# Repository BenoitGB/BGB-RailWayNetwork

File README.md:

# BenoitBG

Electronics and Software Projects for Scale Model Railroad

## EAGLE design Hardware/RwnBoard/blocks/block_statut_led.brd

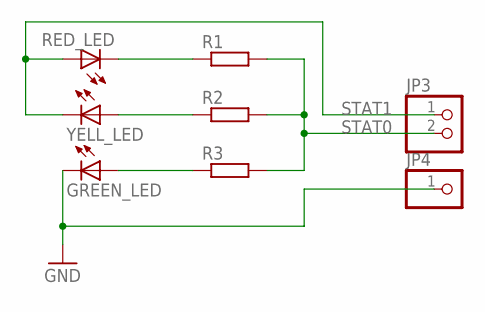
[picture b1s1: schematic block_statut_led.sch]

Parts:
GREEN_LED: LED3MM
JP3: PINHD-1X2; 1X02
JP4: PINHD-1X1; 1X01
R1, R2, R3: R-EU_0207/5V; 0207/5V
RED_LED: LED3MM
YELL_LED: LED3MM

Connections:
GND: GREEN_LED.K (C), JP4.1
unnamed: R1.1, RED_LED.K (C)
unnamed: R2.1, YELL_LED.A
unnamed: GREEN_LED.A, R3.1
STAT0: JP3.2, R1.2, R2.2, R3.2
STAT1: JP3.1, RED_LED.A, YELL_LED.K (C)

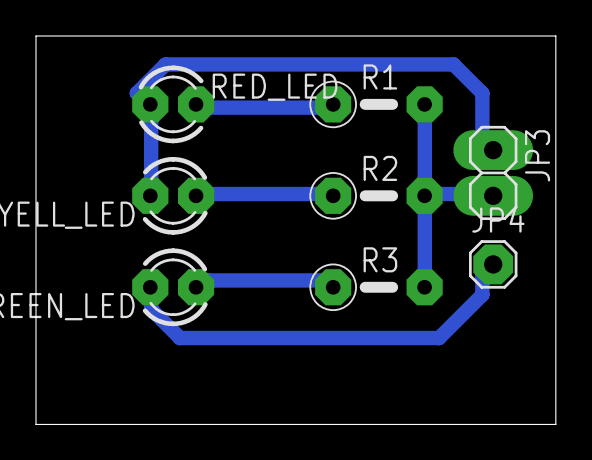
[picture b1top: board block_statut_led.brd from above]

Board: 2 copper layers, 28.9 x 21.6 mm, 8 parts (0 on the bottom side), 6 nets.

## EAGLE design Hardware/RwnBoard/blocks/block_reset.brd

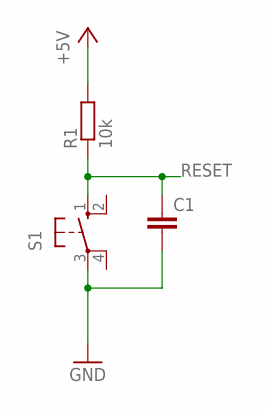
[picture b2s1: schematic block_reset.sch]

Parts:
C1: C-EU050-024X044; C050-024X044
R1: 10k; 0207/10
S1: 10-XX; B3F-10XX

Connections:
+5V: R1.2
GND: C1.2, S1.3
RESET: C1.1, R1.1, S1.1 (S)

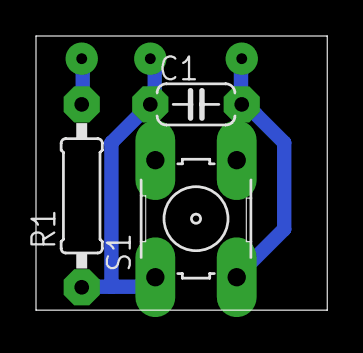
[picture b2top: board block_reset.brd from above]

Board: 2 copper layers, 16.2 x 15.2 mm, 3 parts (0 on the bottom side), 2 nets.

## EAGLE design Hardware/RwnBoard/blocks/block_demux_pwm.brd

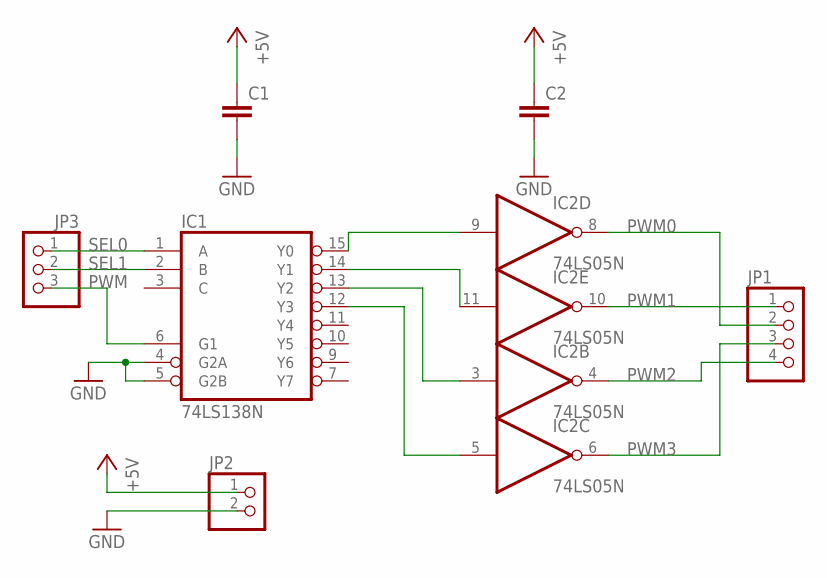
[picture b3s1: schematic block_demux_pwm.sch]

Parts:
C1, C2: C-EU050-025X075; C050-025X075
IC1: 74LS138N; DIL16
IC2: 74LS05N; DIL14
JP1: PINHD-1X4; 1X04
JP2: PINHD-1X2; 1X02
JP3: PINHD-1X3; 1X03

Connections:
GND: C1.2, C2.2, IC1.4 (G2A), IC1.5 (G2B), IC1.8 (GND), IC2.7 (GND), JP2.2
unnamed: IC1.15 (Y0), IC2.9 (I)
unnamed: IC1.14 (Y1), IC2.11 (I)
unnamed: IC1.13 (Y2), IC2.3 (I)
unnamed: IC1.12 (Y3), IC2.5 (I)
PWM: IC1.6 (G1), JP3.3
PWM0: IC2.8 (O), JP1.2
PWM1: IC2.10 (O), JP1.1
PWM2: IC2.4 (O), JP1.4
PWM3: IC2.6 (O), JP1.3
SEL0: IC1.1 (A), JP3.1
SEL1: IC1.2 (B), JP3.2
VCC: C1.1, C2.1, IC1.16 (VCC), IC2.14 (VCC), JP2.1

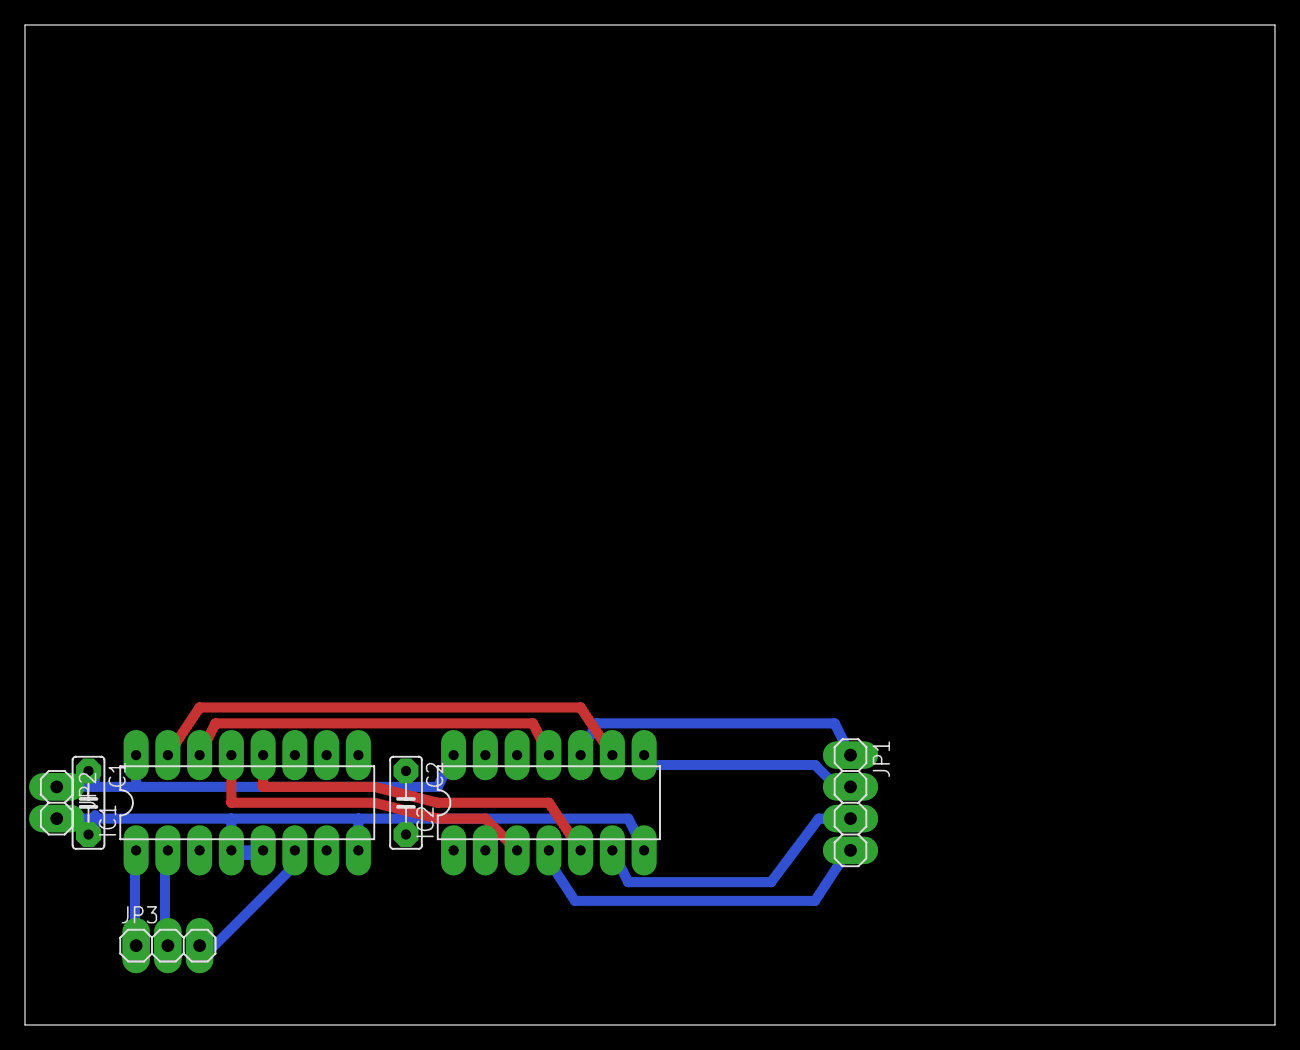
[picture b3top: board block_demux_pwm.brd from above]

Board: 2 copper layers, 100.0 x 80.0 mm, 7 parts (0 on the bottom side), 13 nets.

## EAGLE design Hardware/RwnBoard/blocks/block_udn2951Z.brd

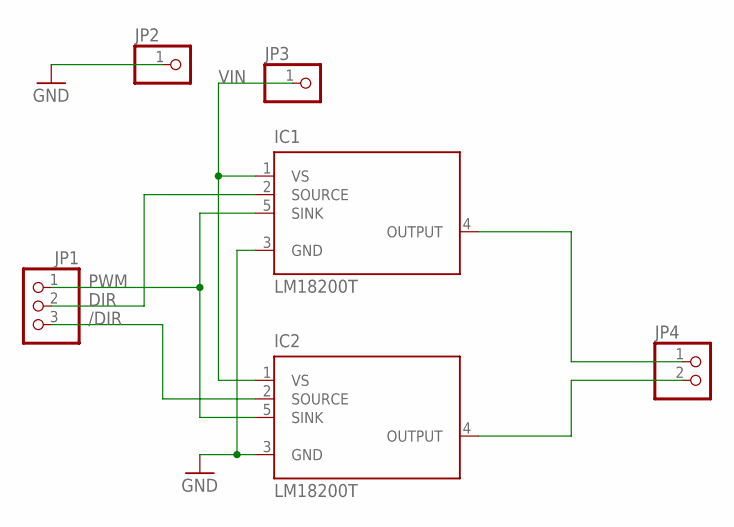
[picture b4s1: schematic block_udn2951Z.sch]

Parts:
IC1, IC2: LM18200T; T05A
JP1: PINHD-1X3; 1X03
JP2, JP3: PINHD-1X1; 1X01
JP4: PINHD-1X2; 1X02

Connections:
/DIR: IC2.2 (SOURCE), JP1.3
DIR: IC1.2 (SOURCE), JP1.2
GND: IC1.3 (GND), IC2.3 (GND), JP2.1
unnamed: IC1.4 (OUTPUT), JP4.1
unnamed: IC2.4 (OUTPUT), JP4.2
PWM: IC1.5 (SINK), IC2.5 (SINK), JP1.1
VIN: IC1.1 (VS), IC2.1 (VS), JP3.1

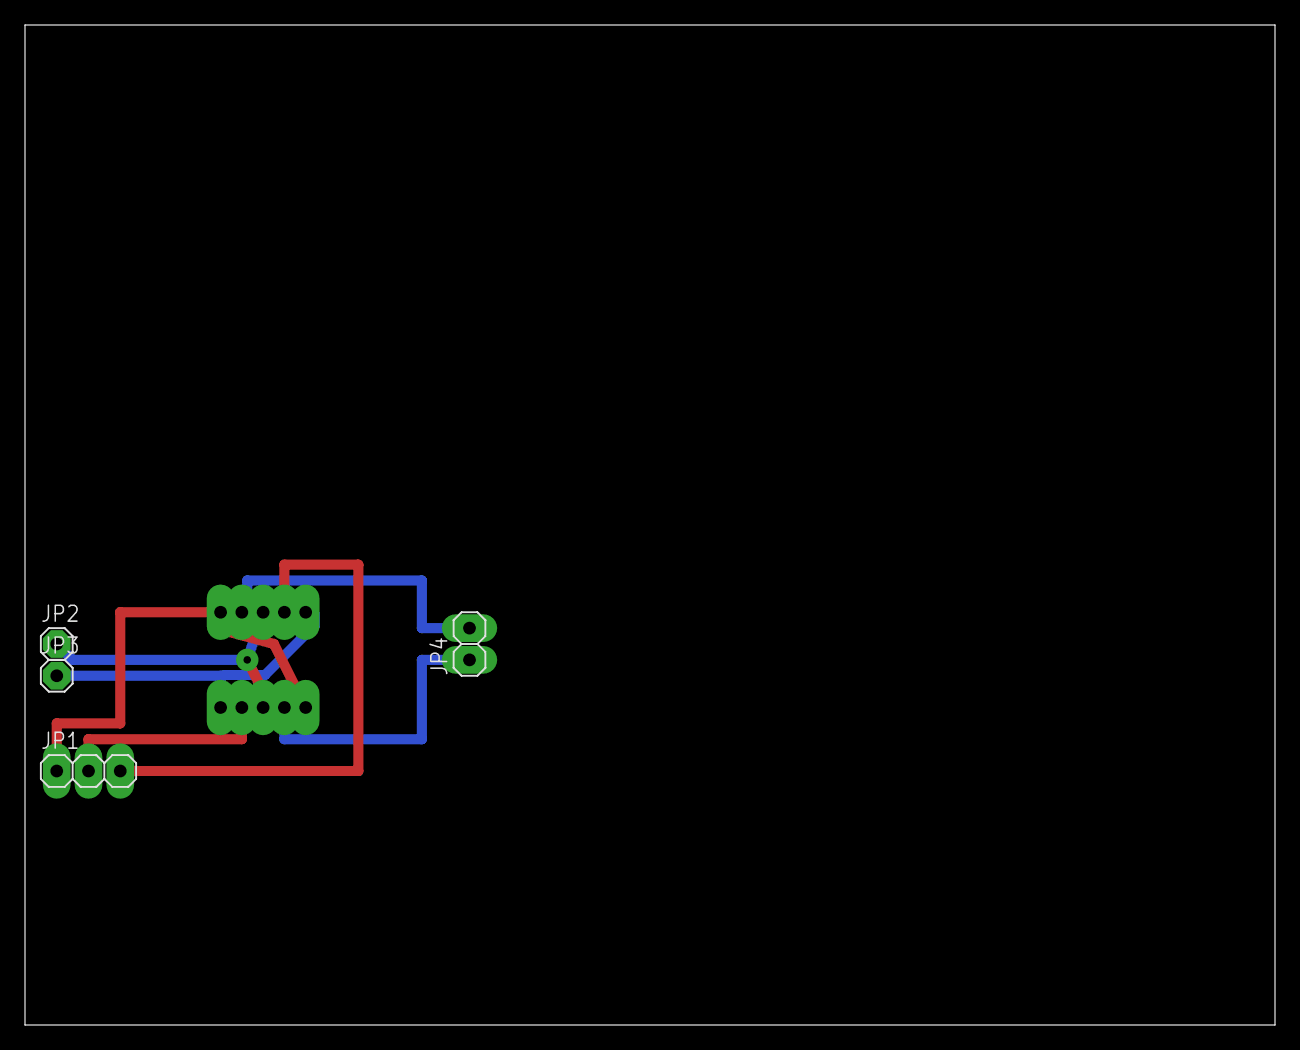
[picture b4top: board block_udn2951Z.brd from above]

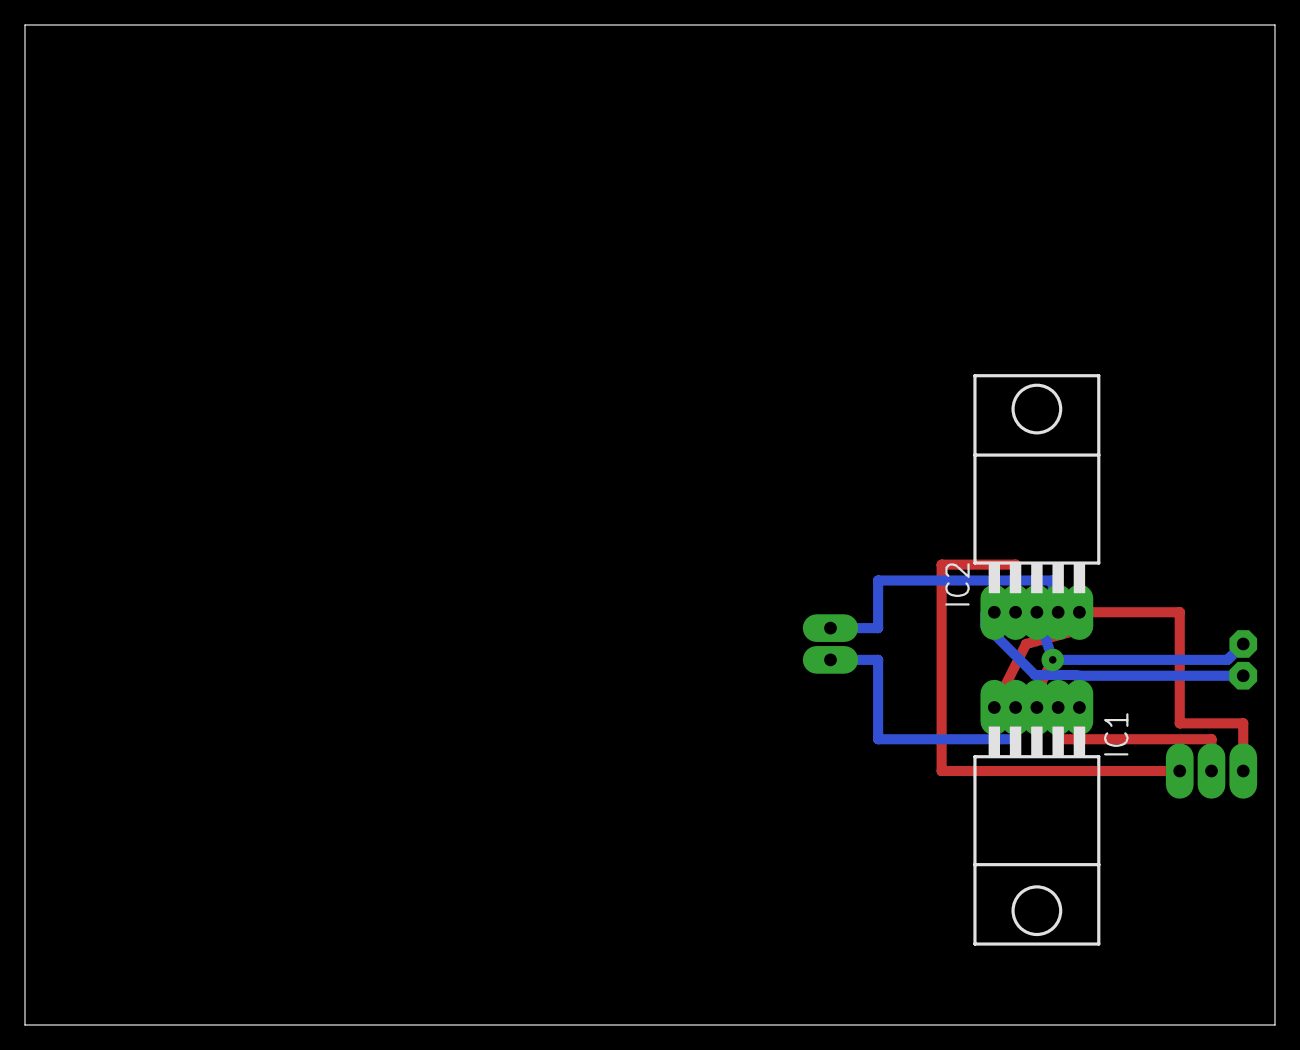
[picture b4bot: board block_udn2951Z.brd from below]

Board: 2 copper layers, 100.0 x 80.0 mm, 6 parts (2 on the bottom side), 7 nets.

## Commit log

2018-08-30 Add basic block shematics and boards
2018-09-08 -Reduce "block_statut_led" layout size for 3D preview -Add images as wiki ,gitPages ressources
2018-09-08 wrong test
2018-09-08 hide gitPages ressources
2018-09-08 Set theme jekyll-theme-slate
2018-09-30 add picture for "dimming effect" wiki page
2018-10-21 Kicad migration
